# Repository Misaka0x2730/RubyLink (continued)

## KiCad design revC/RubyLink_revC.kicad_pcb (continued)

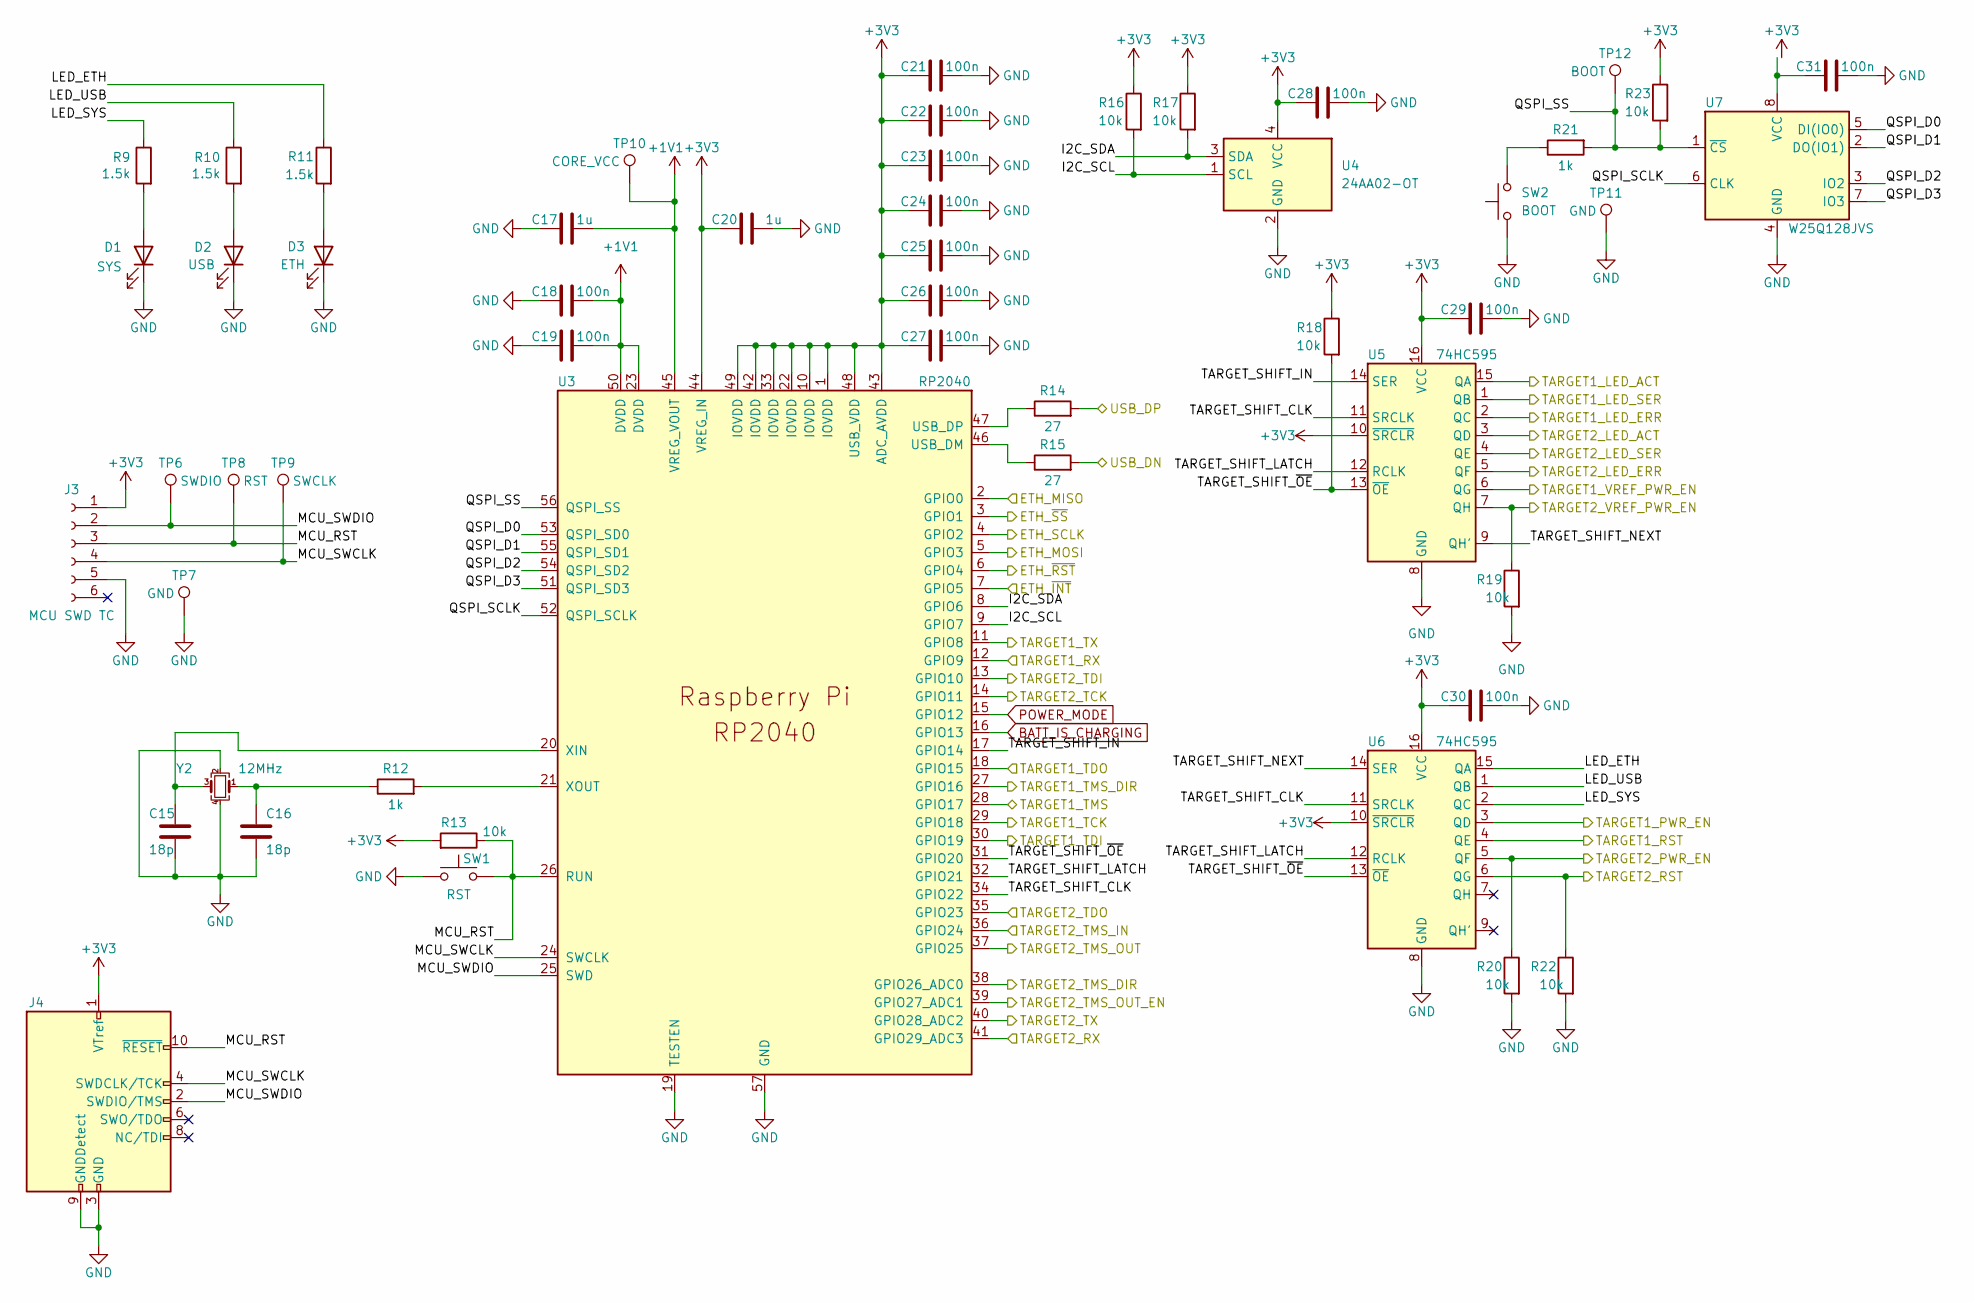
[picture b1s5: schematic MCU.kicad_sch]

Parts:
C15, C16: 18p; C_0402_1005Metric
C17, C20: 1u; C_0402_1005Metric
C18, C19, C21, C22, C23, C24, C25, C26, C27, C28, C29, C30, C31: 100n; C_0402_1005Metric
D1: SYS; LED_D3.0mm
D2: USB; LED_D3.0mm
D3: ETH; LED_D3.0mm; Part Number FYLS-0603UYC
J3: MCU SWD TC; Tag-Connect_TC2030-IDC-FP_2x03_P1.27mm_Vertical
J4: MCU SWD; PinHeader_2x05_P1.27mm_Vertical_SMD
R9, R10, R11: 1.5k; R_0603_1608Metric; Part Number RC0402FR-071K5L
R12, R21: 1k; R_0402_1005Metric
R13, R16, R17, R18, R19, R20, R22, R23: 10k; R_0402_1005Metric
R14, R15: 27; R_0402_1005Metric
SW1: RST; SW_SPST_B3U-1000P
SW2: BOOT; SW_SPST_B3U-1000P
TP6: SWDIO; TestPoint_Pad_D1.0mm
TP7, TP11: GND; TestPoint_Pad_D1.0mm
TP8: RST; TestPoint_Pad_D1.0mm
TP9: SWCLK; TestPoint_Pad_D1.0mm
TP10: CORE_VCC; TestPoint_Pad_D1.0mm
TP12: BOOT; TestPoint_Pad_D1.0mm
U3: RP2040; RP2040-QFN-56
U4: 24AA02-OT; SOT-23-5
U5, U6: 74HC595; SOIC-16_3.9x9.9mm_P1.27mm
U7: W25Q128JVS; SOIC-8_5.23x5.23mm_P1.27mm
Y2: 12MHz; Crystal_SMD_3225-4Pin_3.2x2.5mm

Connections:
+1V1: C17.2, C18.2, C19.2, TP10.1, U3.23 (DVDD), U3.45 (VREG_VOUT), U3.50 (DVDD)
+3V3: C20.1, C21.1, C22.1, C23.1, C24.1, C25.1, C26.1, C27.1, C28.1, C29.1, C30.1, J3.1, J4.1 (VTref), R13.2, R16.1, R17.1, R18.1, R23.1, U3.1 (IOVDD), U3.10 (IOVDD), U3.22 (IOVDD), U3.33 (IOVDD), U3.42 (IOVDD), U3.43 (ADC_AVDD), U3.44 (VREG_IN), U3.48 (USB_VDD), U3.49 (IOVDD), U4.4 (VCC), U5.10 (~SRCLR), U5.16 (VCC), U6.10 (~SRCLR), U6.16 (VCC); also elsewhere on the board
/Input interfaces/ETH_MISO: U3.2 (GPIO0); also elsewhere on the board
/Input interfaces/ETH_MOSI: U3.5 (GPIO3); also elsewhere on the board
/Input interfaces/ETH_SCLK: U3.4 (GPIO2); also elsewhere on the board
/Input interfaces/ETH_~INT: U3.7 (GPIO5); also elsewhere on the board
/Input interfaces/ETH_~RST: U3.6 (GPIO4); also elsewhere on the board
/Input interfaces/ETH_~SS: U3.3 (GPIO1); also elsewhere on the board
/Input interfaces/USB_DN: R15.2; also elsewhere on the board
/Input interfaces/USB_DP: R14.2; also elsewhere on the board
/MCU/I2C_SCL: R16.2, U3.9 (GPIO7), U4.1 (SCL)
/MCU/I2C_SDA: R17.2, U3.8 (GPIO6), U4.3 (SDA)
/MCU/LED_ETH: R11.1, U6.15 (QA)
/MCU/LED_SYS: R9.1, U6.2 (QC)
/MCU/LED_USB: R10.1, U6.1 (QB)
/MCU/MCU_RST: J3.3, J4.10 (~RESET), R13.1, SW1.2, TP8.1, U3.26 (RUN)
/MCU/MCU_SWCLK: J3.4, J4.4 (SWDCLK/TCK), TP9.1, U3.24 (SWCLK)
/MCU/MCU_SWDIO: J3.2, J4.2 (SWDIO/TMS), TP6.1, U3.25 (SWD)
/MCU/QSPI_D0: U3.53 (QSPI_SD0), U7.5 (DI(IO0))
/MCU/QSPI_D1: U3.55 (QSPI_SD1), U7.2 (DO(IO1))
/MCU/QSPI_D2: U3.54 (QSPI_SD2), U7.3 (IO2)
/MCU/QSPI_D3: U3.51 (QSPI_SD3), U7.7 (IO3)
/MCU/QSPI_SCLK: U3.52 (QSPI_SCLK), U7.6 (CLK)
/MCU/QSPI_SS: R21.2, R23.2, TP12.1, U3.56 (QSPI_SS), U7.1 (~CS)
/MCU/TARGET1_LED_ACT: U5.15 (QA); also elsewhere on the board
/MCU/TARGET1_LED_ERR: U5.2 (QC); also elsewhere on the board
/MCU/TARGET1_LED_SER: U5.1 (QB); also elsewhere on the board
/MCU/TARGET1_PWR_EN: U6.3 (QD); also elsewhere on the board
/MCU/TARGET1_RST: U6.4 (QE); also elsewhere on the board
/MCU/TARGET1_RX: U3.12 (GPIO9); also elsewhere on the board
/MCU/TARGET1_TCK: U3.29 (GPIO18); also elsewhere on the board
/MCU/TARGET1_TDI: U3.30 (GPIO19); also elsewhere on the board
/MCU/TARGET1_TDO: U3.18 (GPIO15); also elsewhere on the board
/MCU/TARGET1_TMS: U3.28 (GPIO17); also elsewhere on the board
/MCU/TARGET1_TMS_DIR: U3.27 (GPIO16); also elsewhere on the board
/MCU/TARGET1_TX: U3.11 (GPIO8); also elsewhere on the board
/MCU/TARGET1_VREF_PWR_EN: U5.6 (QG); also elsewhere on the board
/MCU/TARGET2_LED_ACT: U5.3 (QD); also elsewhere on the board
/MCU/TARGET2_LED_ERR: U5.5 (QF); also elsewhere on the board
/MCU/TARGET2_LED_SER: U5.4 (QE); also elsewhere on the board
/MCU/TARGET2_PWR_EN: R20.1, U6.5 (QF); also elsewhere on the board
/MCU/TARGET2_RST: R22.1, U6.6 (QG); also elsewhere on the board
/MCU/TARGET2_RX: U3.41 (GPIO29_ADC3); also elsewhere on the board
/MCU/TARGET2_TCK: U3.14 (GPIO11); also elsewhere on the board
/MCU/TARGET2_TDI: U3.13 (GPIO10); also elsewhere on the board
/MCU/TARGET2_TDO: U3.35 (GPIO23); also elsewhere on the board
/MCU/TARGET2_TMS_DIR: U3.38 (GPIO26_ADC0); also elsewhere on the board
/MCU/TARGET2_TMS_IN: U3.36 (GPIO24); also elsewhere on the board
/MCU/TARGET2_TMS_OUT: U3.37 (GPIO25); also elsewhere on the board
/MCU/TARGET2_TMS_OUT_EN: U3.39 (GPIO27_ADC1); also elsewhere on the board
/MCU/TARGET2_TX: U3.40 (GPIO28_ADC2); also elsewhere on the board
/MCU/TARGET2_VREF_PWR_EN: R19.1, U5.7 (QH); also elsewhere on the board
/MCU/TARGET_SHIFT_CLK: U3.34 (GPIO22), U5.11 (SRCLK), U6.11 (SRCLK)
/MCU/TARGET_SHIFT_IN: U3.17 (GPIO14), U5.14 (SER)
/MCU/TARGET_SHIFT_LATCH: U3.32 (GPIO21), U5.12 (RCLK), U6.12 (RCLK)
/MCU/TARGET_SHIFT_NEXT: U5.9 (QH'), U6.14 (SER)
/MCU/TARGET_SHIFT_~OE: R18.2, U3.31 (GPIO20), U5.13 (~OE), U6.13 (~OE)
BATT_IS_CHARGING: U3.16 (GPIO13); also elsewhere on the board
GND: C15.2, C16.2, C17.1, C18.1, C19.1, C20.2, C21.2, C22.2, C23.2, C24.2, C25.2, C26.2, C27.2, C28.2, C29.2, C30.2, C31.2, D1.1 (K), D2.1 (K), D3.1 (K), J3.5, J4.3 (GND), J4.5 (GND), J4.9 (GNDDetect), R19.2, R20.2, R22.2, SW1.1, SW2.1, TP7.1, TP11.1, U3.19 (TESTEN), U3.57 (GND), U4.2 (GND), U5.8 (GND), U6.8 (GND), U7.4 (GND), Y2.2, Y2.4; also elsewhere on the board
unnamed: C15.1, U3.20 (XIN), Y2.3
unnamed: C16.1, R12.1, Y2.1
unnamed: C31.1, U7.8 (VCC)
unnamed: D1.2 (A), R9.2
unnamed: D2.2 (A), R10.2
unnamed: D3.2 (A), R11.2
unnamed: R12.2, U3.21 (XOUT)
unnamed: R14.1, U3.47 (USB_DP)
unnamed: R15.1, U3.46 (USB_DM)
unnamed: R21.1, SW2.2
POWER_MODE: U3.15 (GPIO12); also elsewhere on the board

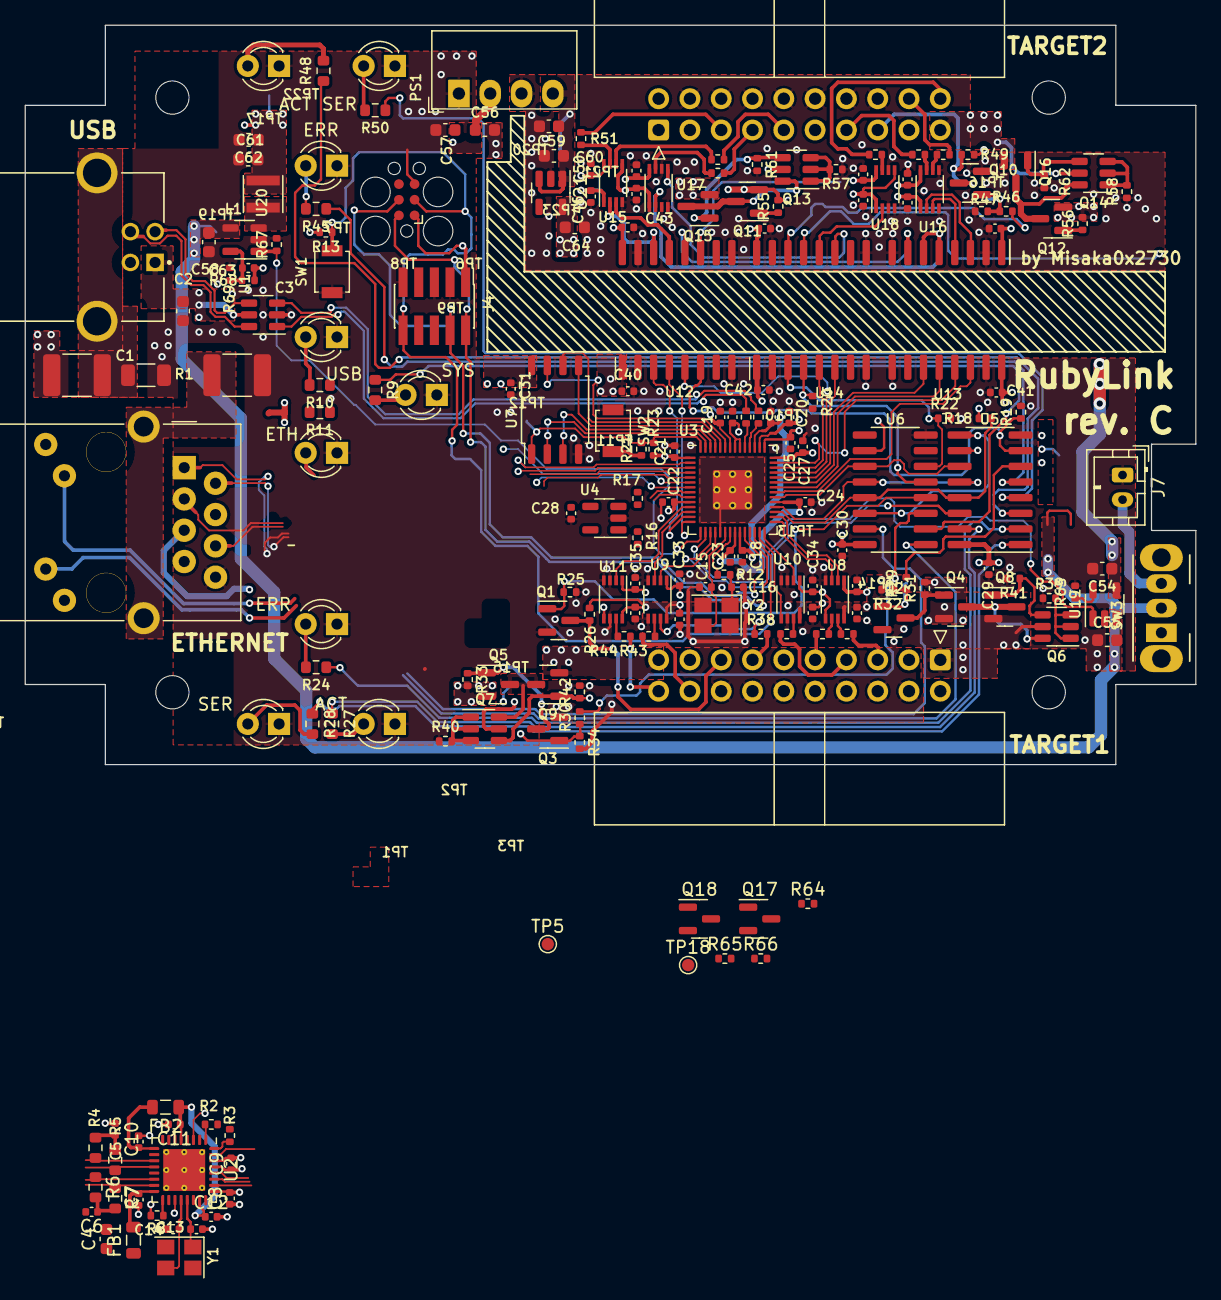
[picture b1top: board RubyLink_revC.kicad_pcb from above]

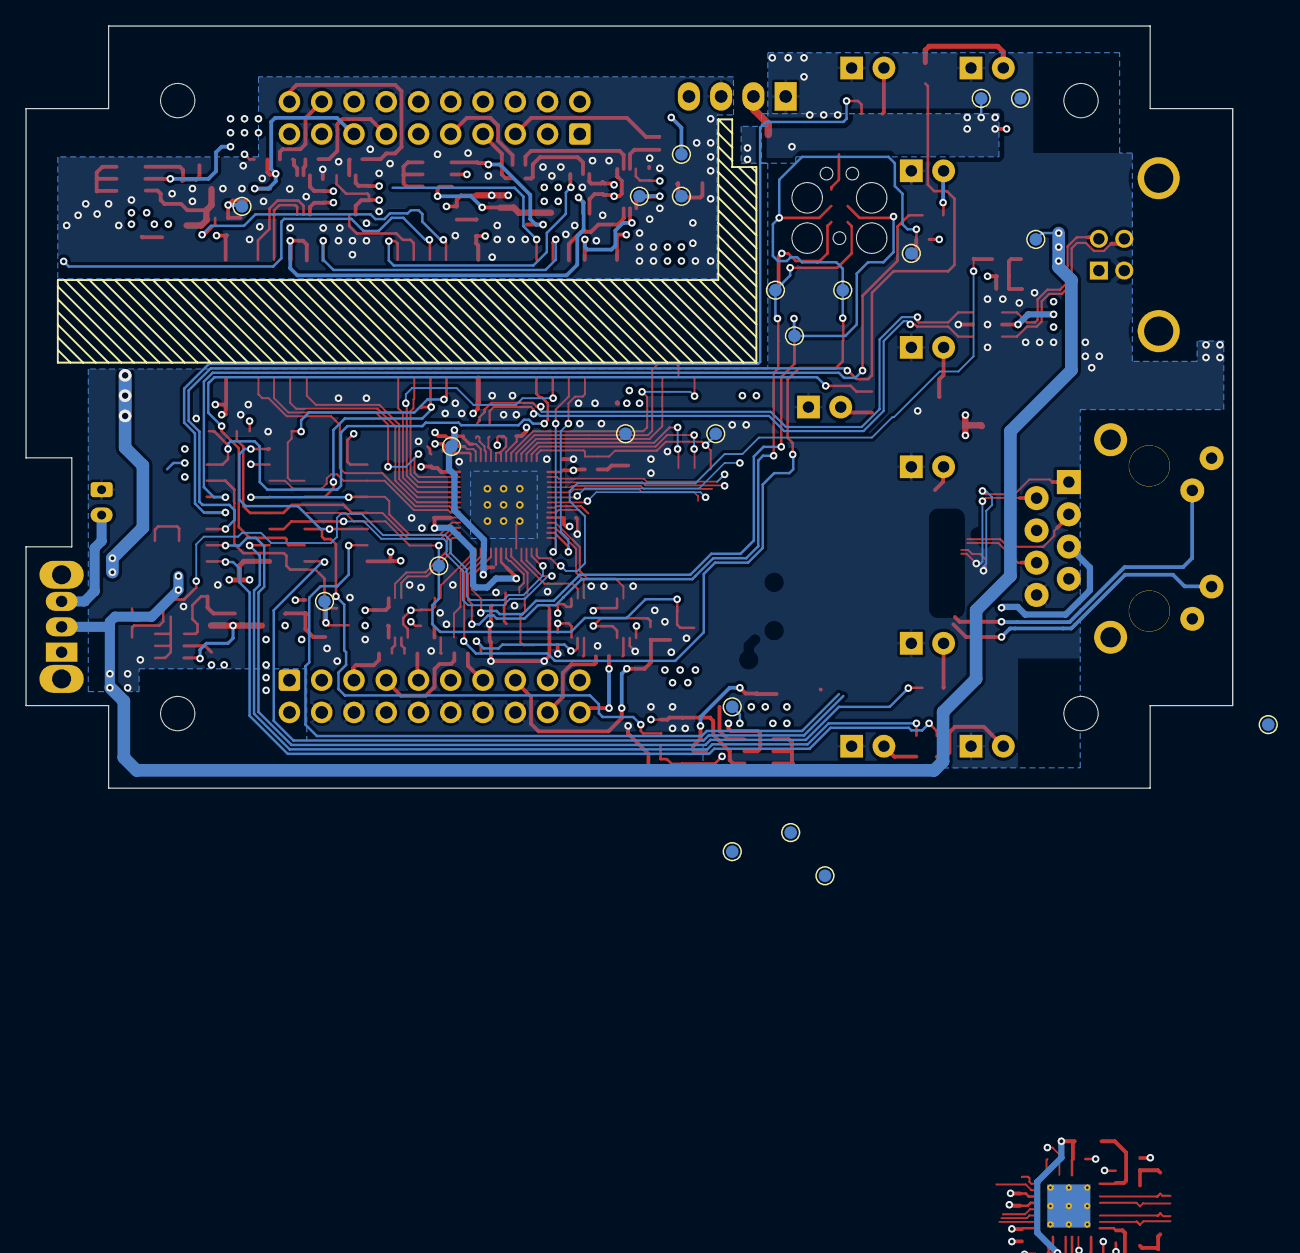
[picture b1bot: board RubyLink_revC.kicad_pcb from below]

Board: 4 copper layers, 95.0 x 60.0 mm, 224 parts (21 on the bottom side), 166 nets.

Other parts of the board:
REF1, REF2, REF3, REF4: MountingHole_2.7mm_M2.5

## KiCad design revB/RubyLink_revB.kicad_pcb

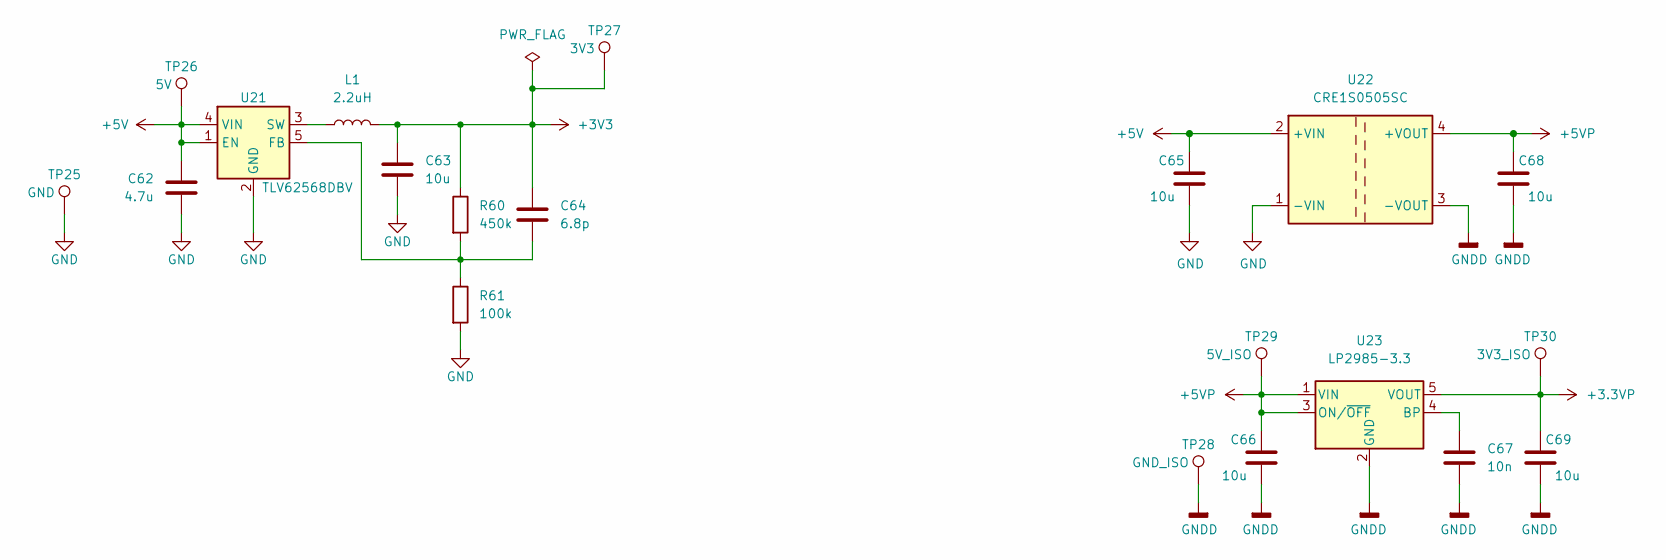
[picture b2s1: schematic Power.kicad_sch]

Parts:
C62: 4.7u; C_0603_1608Metric
C63: 10u; C_0603_1608Metric
C64: 6.8p; C_0402_1005Metric
C65, C66, C68, C69: 10u; C_0603_1608Metric; Part Number CC0603KRX5R6BB106
C67: 10n; C_0402_1005Metric
L1: 2.2uH; L_Taiyo-Yuden_NR-30xx; Part number NR3012T2R2M
R60: 450k; R_0402_1005Metric
R61: 100k; R_0402_1005Metric
TP25: GND; TestPoint_Pad_D1.0mm
TP26: 5V; TestPoint_Pad_D1.0mm
TP27: 3V3; TestPoint_Pad_D1.0mm
TP28: GND_ISO; TestPoint_Pad_D1.0mm
TP29: 5V_ISO; TestPoint_Pad_D1.0mm
TP30: 3V3_ISO; TestPoint_Pad_D1.0mm
U21: TLV62568DBV; SOT-23-5
U22: CRE1S0505SC; Converter_DCDC_Murata_CRE1xxxxxxSC_THT
U23: LP2985-3.3; SOT-23-5

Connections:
+3.3VP: C69.1, TP30.1, U23.5 (VOUT); also elsewhere on the board
+3V3: C63.1, C64.1, L1.2, R60.1, TP27.1; also elsewhere on the board
+5V: C62.2, C65.1, TP26.1, U21.1 (EN), U21.4 (VIN), U22.2 (+VIN); also elsewhere on the board
+5VP: C66.1, C68.1, TP29.1, U22.4 (+VOUT), U23.1 (VIN), U23.3 (ON/~OFF); also elsewhere on the board
GND: C62.1, C63.2, C65.2, R61.2, TP25.1, U21.2 (GND), U22.1 (-VIN); also elsewhere on the board
GNDD: C66.2, C67.2, C68.2, C69.2, TP28.1, U22.3 (-VOUT), U23.2 (GND); also elsewhere on the board
unnamed: C64.2, R60.2, R61.1, U21.5 (FB)
unnamed: C67.1, U23.4 (BP)
unnamed: L1.1, U21.3 (SW)

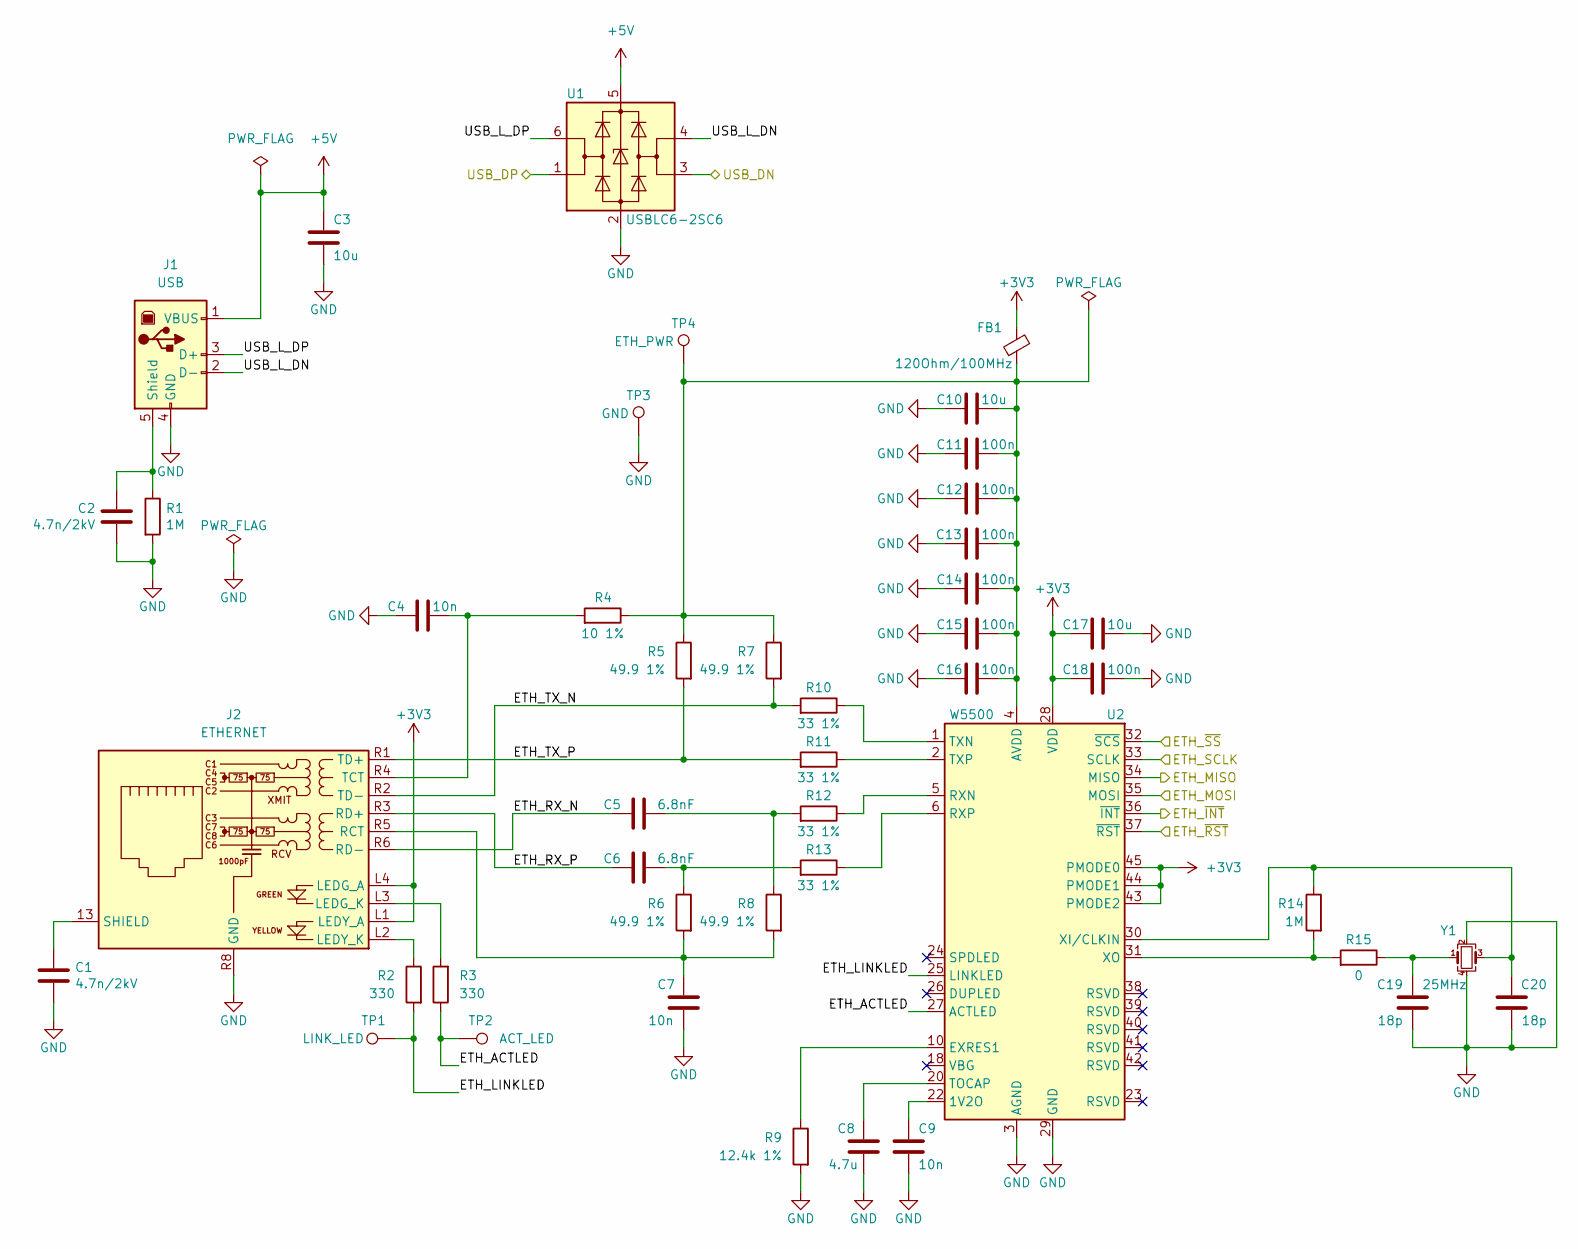
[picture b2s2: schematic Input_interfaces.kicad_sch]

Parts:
C1, C2: 4.7n/2kV; C_1812_4532Metric; Part Number 202S43W472KV4E
C3, C10, C17: 10u; C_0603_1608Metric
C4, C7, C9: 10n; C_0402_1005Metric
C5, C6: 6.8nF; C_0402_1005Metric
C8: 4.7u; C_0603_1608Metric
C11, C12, C13, C14, C15, C16, C18: 100n; C_0402_1005Metric
C19, C20: 18p; C_0402_1005Metric
FB1: 120Ohm/100MHz; L_0805_2012Metric
J1: USB; TE_292304-2
J2: ETHERNET; RJ45_Amphenol_RJMG1BD3B8K1ANR
R1: 1M; R_1206_3216Metric; Part Number 1206W4J0105T5E
R2, R3: 330; R_0402_1005Metric
R4: 10 1%; R_0603_1608Metric
R5, R6, R7, R8: 49.9 1%; R_0603_1608Metric
R9: 12.4k 1%; R_0402_1005Metric
R10, R11, R12, R13: 33 1%; R_0603_1608Metric
R14: 1M; R_0402_1005Metric
R15: 0; R_0402_1005Metric
TP1: LINK_LED; TestPoint_Pad_D1.0mm
TP2: ACT_LED; TestPoint_Pad_D1.0mm
TP3: GND; TestPoint_Pad_D1.0mm
TP4: ETH_PWR; TestPoint_Pad_D1.0mm
U1: USBLC6-2SC6; SOT-23-6
U2: W5500; LQFP-48_7x7mm_P0.5mm
Y1: 25MHz; Crystal_SMD_3225-4Pin_3.2x2.5mm

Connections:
+3V3: C17.1, C18.1, FB1.1, J2.L1 (LEDY_A), J2.L4 (LEDG_A), U2.28 (VDD), U2.43 (PMODE2), U2.44 (PMODE1), U2.45 (PMODE0); also elsewhere on the board
+5V: C3.1, J1.1 (VBUS), U1.5 (VBUS); also elsewhere on the board
/Input interfaces/ETH_ACTLED: R3.1, TP2.1, U2.27 (ACTLED)
/Input interfaces/ETH_LINKLED: R2.2, TP1.1, U2.25 (LINKLED)
/Input interfaces/ETH_MISO: U2.34 (MISO); also elsewhere on the board
/Input interfaces/ETH_MOSI: U2.35 (MOSI); also elsewhere on the board
/Input interfaces/ETH_RX_N: C5.1, J2.R6 (RD-)
/Input interfaces/ETH_RX_P: C6.1, J2.R3 (RD+)
/Input interfaces/ETH_SCLK: U2.33 (SCLK); also elsewhere on the board
/Input interfaces/ETH_TX_N: J2.R2 (TD-), R7.2, R10.2
/Input interfaces/ETH_TX_P: J2.R1 (TD+), R5.2, R11.2
/Input interfaces/ETH_~INT: U2.36 (~INT); also elsewhere on the board
/Input interfaces/ETH_~RST: U2.37 (~RST); also elsewhere on the board
/Input interfaces/ETH_~SS: U2.32 (~SCS); also elsewhere on the board
/Input interfaces/USB_DN: U1.3 (I/O2); also elsewhere on the board
/Input interfaces/USB_DP: U1.1 (I/O1); also elsewhere on the board
/Input interfaces/USB_L_DN: J1.2 (D-), U1.4 (I/O2)
/Input interfaces/USB_L_DP: J1.3 (D+), U1.6 (I/O1)
GND: C1.1, C2.1, C3.2, C4.1, C7.2, C8.2, C9.2, C10.1, C11.1, C12.1, C13.1, C14.1, C15.1, C16.1, C17.2, C18.2, C19.2, C20.2, J1.4 (GND), J2.R8 (GND), R1.2, R9.2, TP3.1, U1.2 (GND), U2.3 (AGND), U2.9 (AGND), U2.14 (AGND), U2.16 (AGND), U2.19 (AGND), U2.29 (GND), U2.48 (AGND), Y1.2, Y1.4; also elsewhere on the board
unnamed: C1.2, J2.13 (SHIELD)
unnamed: C2.2, J1.5 (Shield), R1.1
unnamed: C4.2, J2.R4 (TCT), R4.2
unnamed: C5.2, R8.1, R12.2
unnamed: C6.2, R6.1, R13.2
unnamed: C7.1, J2.R5 (RCT), R6.2, R8.2
unnamed: C8.1, U2.20 (TOCAP)
unnamed: C9.1, U2.22 (1V2O)
unnamed: C10.2, C11.2, C12.2, C13.2, C14.2, C15.2, C16.2, FB1.2, R4.1, R5.1, R7.1, TP4.1, U2.4 (AVDD), U2.8 (AVDD), U2.11 (AVDD), U2.15 (AVDD), U2.17 (AVDD), U2.21 (AVDD)
unnamed: C19.1, R15.1, Y1.1
unnamed: C20.1, R14.1, U2.30 (XI/CLKIN), Y1.3
unnamed: J2.L2 (LEDY_K), R2.1
unnamed: J2.L3 (LEDG_K), R3.2
unnamed: R9.1, U2.10 (EXRES1)
unnamed: R10.1, U2.1 (TXN)
unnamed: R11.1, U2.2 (TXP)
unnamed: R12.1, U2.5 (RXN)
unnamed: R13.1, U2.6 (RXP)
unnamed: R14.2, R15.2, U2.31 (XO)

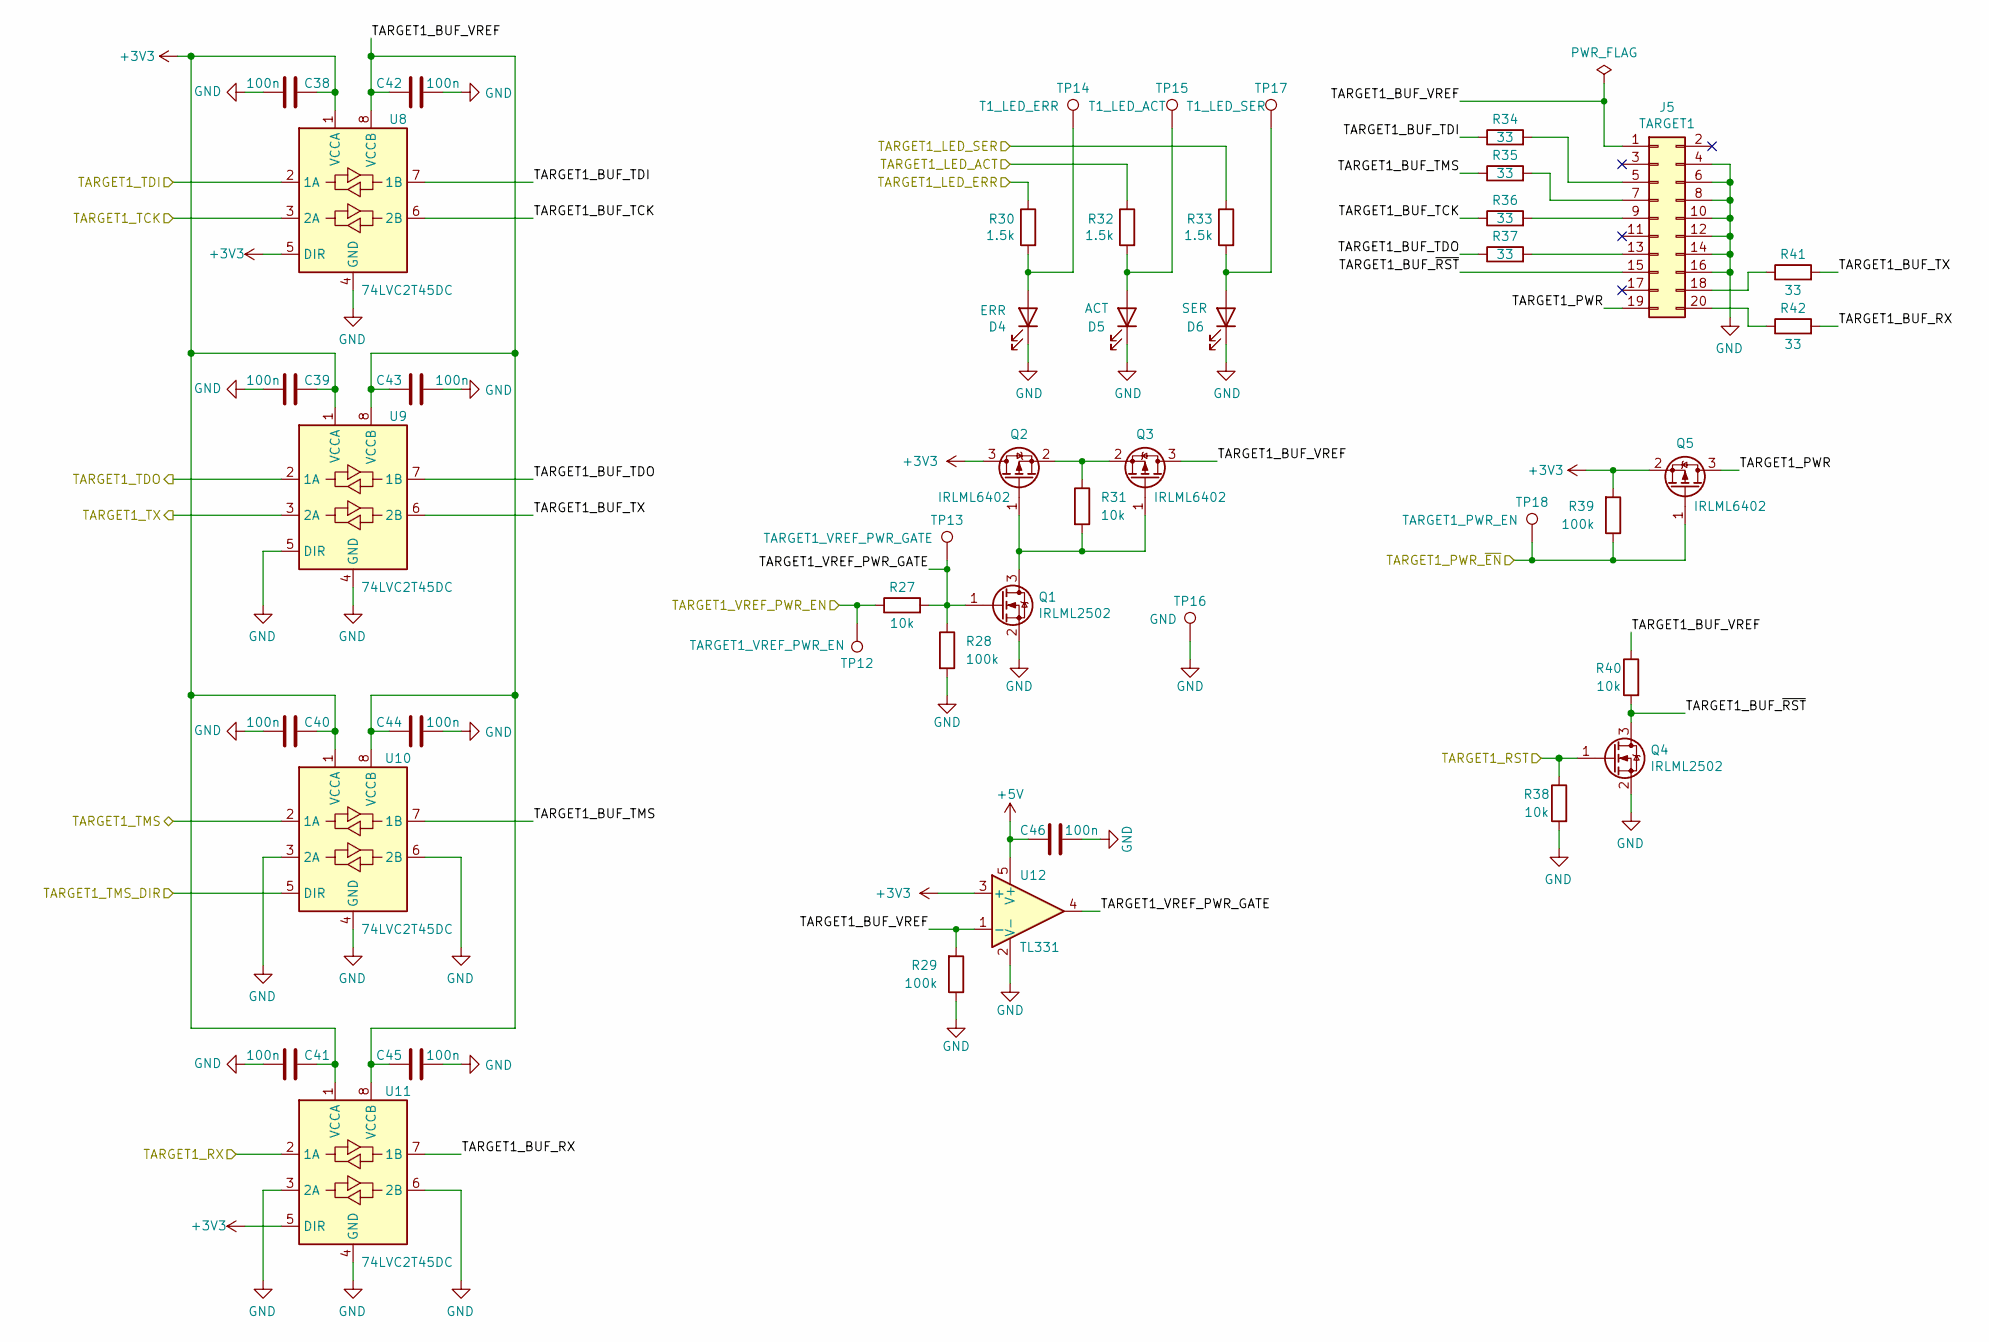
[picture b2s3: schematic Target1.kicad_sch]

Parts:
C38, C39, C40, C41, C42, C43, C44, C45: 100n; C_0402_1005Metric; Part Number CC0402KRX7R7BB104
C46: 100n; C_0402_1005Metric
D4: ERR; LED_D3.0mm
D5: ACT; LED_D3.0mm
D6: SER; LED_D3.0mm; Part Number FYLS-0603UYC
J5: TARGET1; IDC-Header_2x10_P2.54mm_Horizontal; Part Number BH-20R
Q1, Q4: IRLML2502; SOT-23; Part Number IRLML2502TRPBF
Q2, Q3, Q5: IRLML6402; SOT-23
R27, R31: 10k; R_0402_1005Metric
R28, R29, R39: 100k; R_0402_1005Metric
R30, R32, R33: 1.5k; R_0402_1005Metric; Part Number RC0402FR-071K5L
R34, R35, R36, R37, R41, R42: 33; R_0402_1005Metric; Part Number RC0402FR-07100KL
R38, R40: 10k; R_0402_1005Metric; Part Number RC0402FR-0710KL
TP12: TARGET1_VREF_PWR_EN; TestPoint_Pad_D1.0mm
TP13: TARGET1_VREF_PWR_GATE; TestPoint_Pad_D1.0mm
TP14: T1_LED_ERR; TestPoint_Pad_D1.0mm
TP15: T1_LED_ACT; TestPoint_Pad_D1.0mm
TP16: GND; TestPoint_Pad_D1.0mm
TP17: T1_LED_SER; TestPoint_Pad_D1.0mm
TP18: TARGET1_PWR_EN; TestPoint_Pad_D1.0mm
U8, U9, U10, U11: 74LVC2T45DC; VSSOP-8_2.3x2mm_P0.5mm; Part Number SN74LVC2T45DCUR
U12: TL331; SOT-23-5

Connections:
+3V3: C38.1, C39.1, C40.1, C41.1, Q2.3 (D), Q5.2 (S), R39.2, U8.1 (VCCA), U8.5 (DIR), U9.1 (VCCA), U10.1 (VCCA), U11.1 (VCCA), U11.5 (DIR), U12.3 (+); also elsewhere on the board
+5V: C46.1, U12.5 (V+); also elsewhere on the board
/MCU/TARGET1_LED_ACT: R32.1; also elsewhere on the board
/MCU/TARGET1_LED_ERR: R30.1; also elsewhere on the board
/MCU/TARGET1_LED_SER: R33.1; also elsewhere on the board
/MCU/TARGET1_PWR_~EN: Q5.1 (G), R39.1, TP18.1; also elsewhere on the board
/MCU/TARGET1_RST: Q4.1 (G), R38.1; also elsewhere on the board
/MCU/TARGET1_RX: U9.3 (2A); also elsewhere on the board
/MCU/TARGET1_TCK: U8.3 (2A); also elsewhere on the board
/MCU/TARGET1_TDI: U8.2 (1A); also elsewhere on the board
/MCU/TARGET1_TDO: U9.2 (1A); also elsewhere on the board
/MCU/TARGET1_TMS: U10.2 (1A); also elsewhere on the board
/MCU/TARGET1_TMS_DIR: U10.5 (DIR); also elsewhere on the board
/MCU/TARGET1_TX: U11.2 (1A); also elsewhere on the board
/MCU/TARGET1_VREF_PWR_EN: R27.1, TP12.1; also elsewhere on the board
/Target1/TARGET1_BUF_RX: R42.2, U11.7 (1B)
/Target1/TARGET1_BUF_TCK: R36.1, U8.6 (2B)
/Target1/TARGET1_BUF_TDI: R34.1, U8.7 (1B)
/Target1/TARGET1_BUF_TDO: R37.1, U9.7 (1B)
/Target1/TARGET1_BUF_TMS: R35.1, U10.7 (1B)
/Target1/TARGET1_BUF_TX: R41.2, U9.6 (2B)
/Target1/TARGET1_BUF_VREF: C42.2, C43.2, C44.2, C45.2, J5.1, Q3.3 (D), R29.2, R40.1, U8.8 (VCCB), U9.8 (VCCB), U10.8 (VCCB), U11.8 (VCCB), U12.1 (-)
/Target1/TARGET1_BUF_~RST: J5.15, Q4.3 (D), R40.2
/Target1/TARGET1_PWR: J5.19, Q5.3 (D)
/Target1/TARGET1_VREF_PWR_GATE: Q1.1 (G), R27.2, R28.1, TP13.1, U12.4
GND: C38.2, C39.2, C40.2, C41.2, C42.1, C43.1, C44.1, C45.1, C46.2, D4.1 (K), D5.1 (K), D6.1 (K), J5.4, J5.6, J5.8, J5.10, J5.12, J5.14, J5.16, Q1.2 (S), Q4.2 (S), R28.2, R29.1, R38.2, TP16.1, U8.4 (GND), U9.4 (GND), U9.5 (DIR), U10.3 (2A), U10.4 (GND), U10.6 (2B), U11.3 (2A), U11.4 (GND), U11.6 (2B), U12.2 (V-); also elsewhere on the board
unnamed: D4.2 (A), R30.2, TP14.1
unnamed: D5.2 (A), R32.2, TP15.1
unnamed: D6.2 (A), R33.2, TP17.1
unnamed: J5.5, R34.2
unnamed: J5.7, R35.2
unnamed: J5.9, R36.2
unnamed: J5.13, R37.2
unnamed: J5.18, R41.1
unnamed: J5.20, R42.1
unnamed: Q1.3 (D), Q2.1 (G), Q3.1 (G), R31.2
unnamed: Q2.2 (S), Q3.2 (S), R31.1
